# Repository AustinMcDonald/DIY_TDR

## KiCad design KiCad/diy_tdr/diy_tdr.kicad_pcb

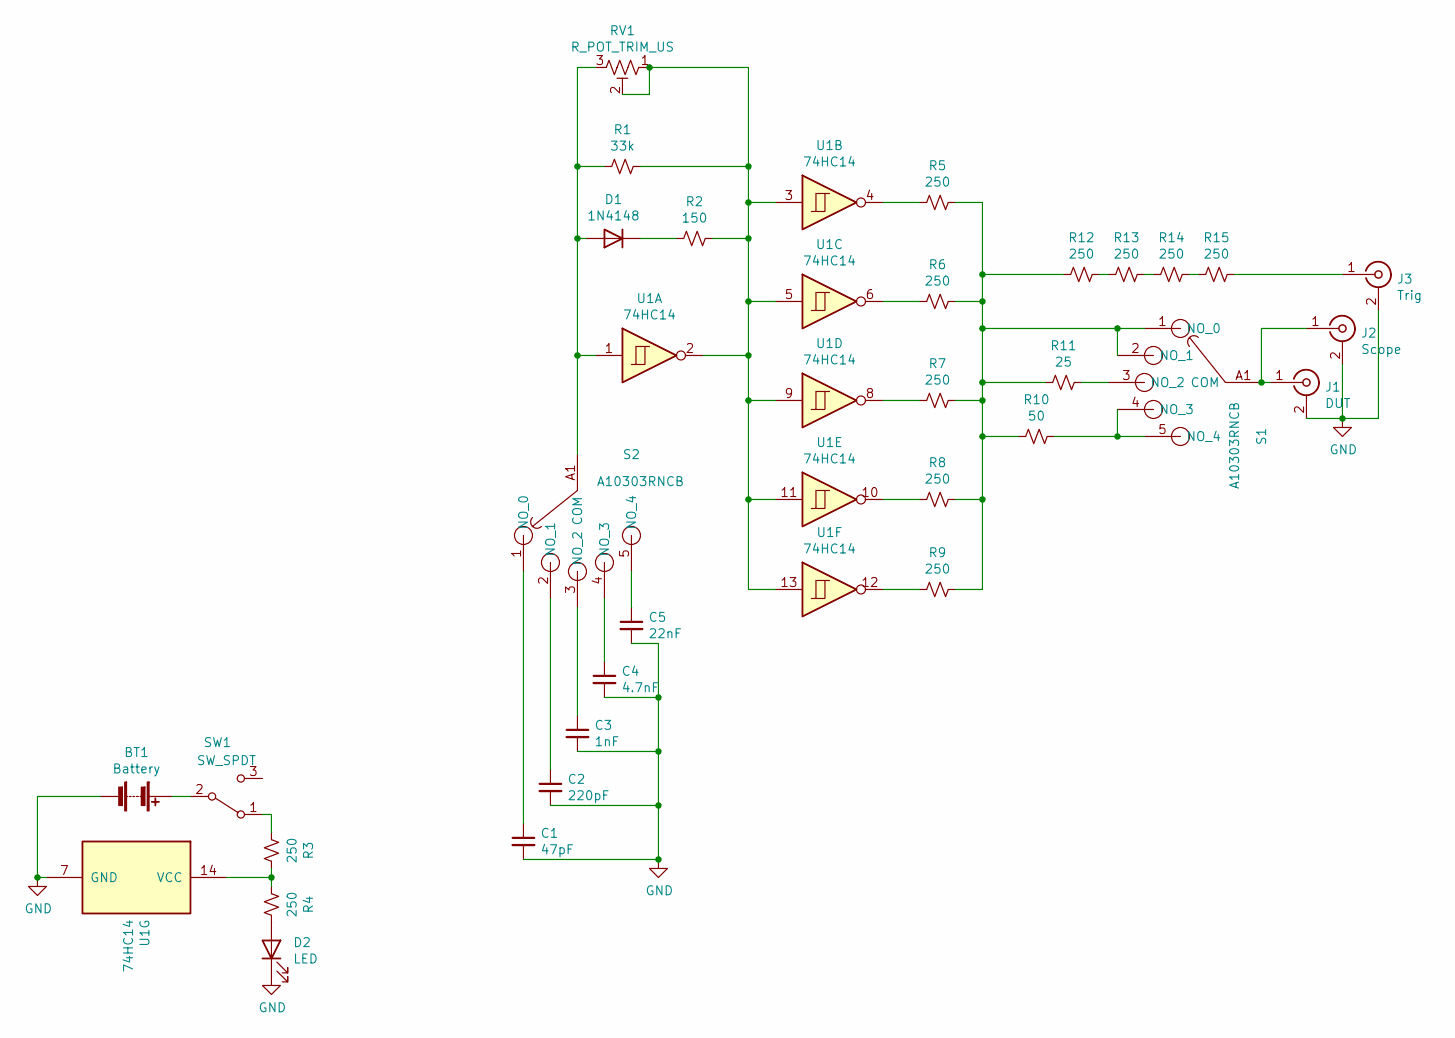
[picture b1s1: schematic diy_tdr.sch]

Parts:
BT1: Battery; 2479
C1: 47pF; C_0805_2012Metric_Pad1.18x1.45mm_HandSolder
C2: 220pF; C_0805_2012Metric_Pad1.18x1.45mm_HandSolder
C3: 1nF; C_0805_2012Metric_Pad1.18x1.45mm_HandSolder
C4: 4.7nF; C_0805_2012Metric_Pad1.18x1.45mm_HandSolder
C5: 22nF; C_0805_2012Metric_Pad1.18x1.45mm_HandSolder
D1: 1N4148; D_DO-35_SOD27_P7.62mm_Horizontal
D2: LED; LED_D3.0mm
J1: DUT; 731375003
J2: Scope; 731375003
J3: Trig; 731375003
R1: 33k; R_0805_2012Metric_Pad1.20x1.40mm_HandSolder
R2: 150; R_0805_2012Metric_Pad1.20x1.40mm_HandSolder
R3, R4, R5, R6, R7, R8, R9, R12, R13, R14, R15: 250; R_0805_2012Metric_Pad1.20x1.40mm_HandSolder
R10: 50; R_0805_2012Metric_Pad1.20x1.40mm_HandSolder
R11: 25; R_0805_2012Metric_Pad1.20x1.40mm_HandSolder
RV1: R_POT_TRIM_US; Potentiometer_Runtron_RM-065_Vertical
S1, S2: A10303RNCB; A10405RNCQE; Mouser Part Number 611-A10303RNCB
SW1: SW_SPDT; M2012LL1W03
U1: 74HC14; SOIC-14_3.9x8.7mm_P1.27mm

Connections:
GND: BT1.2 (-), C1.2, C2.2, C3.2, C4.2, C5.2, D2.1 (K), J1.2 (Ext), J2.2 (Ext), J3.2 (Ext), U1.7 (GND); also elsewhere on the board
unnamed: BT1.1 (+), SW1.2 (B)
unnamed: C1.1, S2.1 (NO_0)
unnamed: C2.1, S2.2 (NO_1)
unnamed: C3.1, S2.3 (NO_2)
unnamed: C4.1, S2.4 (NO_3)
unnamed: C5.1, S2.5 (NO_4)
unnamed: D1.1 (K), R2.2
unnamed: D1.2 (A), R1.2, RV1.3, S2.A1 (COM), U1.1
unnamed: D2.2 (A), R4.1
unnamed 10: J1.1 (In), J2.1 (In), S1.A1 (COM); also elsewhere on the board
unnamed 11: J3.1 (In), R15.1; also elsewhere on the board
unnamed: R1.1, R2.1, RV1.1, RV1.2, U1.2, U1.3, U1.5, U1.9, U1.11, U1.13
unnamed: R3.1, R4.2, U1.14 (VCC)
unnamed: R3.2, SW1.1 (A)
unnamed: R5.2, U1.4
unnamed: R6.2, U1.6
unnamed: R7.2, U1.8
unnamed: R8.2, U1.10
unnamed: R9.2, U1.12
unnamed: R10.1, S1.4 (NO_3), S1.5 (NO_4)
unnamed: R5.1, R6.1, R7.1, R8.1, R9.1, R10.2, R11.2, R12.2, S1.1 (NO_0), S1.2 (NO_1)
unnamed: R11.1, S1.3 (NO_2)
unnamed: R12.1, R13.2
unnamed: R13.1, R14.2
unnamed: R14.1, R15.2
unnamed: S1.6 (NO_CONNECTION_1), S1.7 (NO_CONNECTION_2), S1.8 (NO_CONNECTION_3), S1.9 (NO_CONNECTION_4), S1.10 (NO_CONNECTION_5), S1.11 (NO_CONNECTION_6), S1.12 (NO_CONNECTION_7)
unnamed: S2.6 (NO_CONNECTION_1), S2.7 (NO_CONNECTION_2), S2.8 (NO_CONNECTION_3), S2.9 (NO_CONNECTION_4), S2.10 (NO_CONNECTION_5), S2.11 (NO_CONNECTION_6), S2.12 (NO_CONNECTION_7)

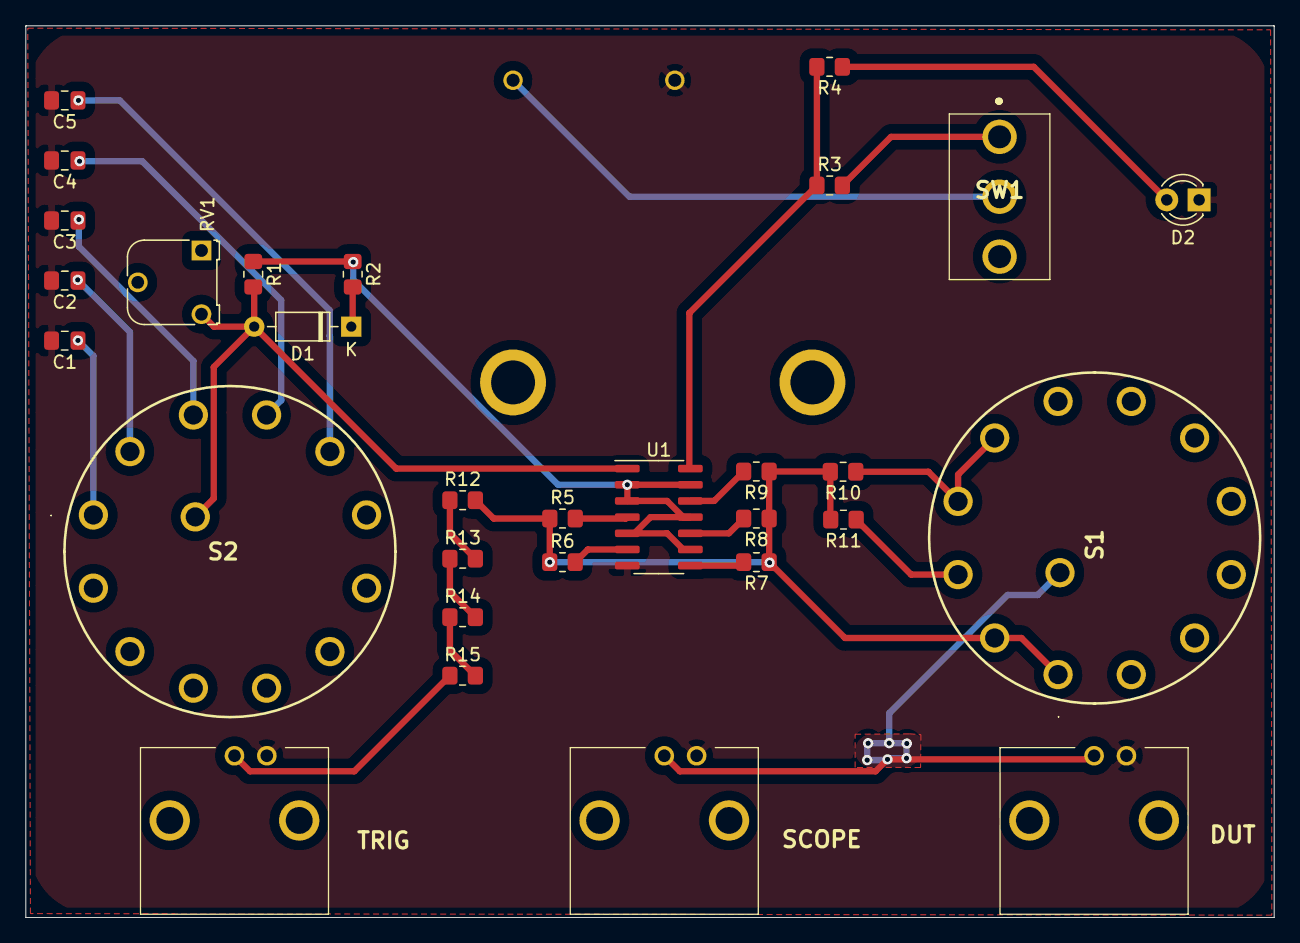
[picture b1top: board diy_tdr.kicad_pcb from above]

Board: 2 copper layers, 98.0 x 70.0 mm, 31 parts (1 on the bottom side), 28 nets.

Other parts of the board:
DUT: DUT; 731375003
SCOPE: Scope; 731375003
TRIG: Trig; 731375003

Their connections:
GND: DUT.2, SCOPE.2, TRIG.2; also elsewhere on the board
unnamed 10: DUT.1, SCOPE.1; also elsewhere on the board
unnamed 11: TRIG.1; also elsewhere on the board

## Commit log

2022-01-25 first
2022-01-26 Foot Prints Added
2022-01-27 finished layout
